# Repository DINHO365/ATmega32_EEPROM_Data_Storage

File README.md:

# ATmega32 EEPROM Data Logging and Configuration Storage System

Demonstrates internal EEPROM read/write on the ATmega32 by letting a
user increment/decrement a value in RAM, save it to EEPROM, read it
back, clear it, and recover it after reset or a power cycle.

## Repository structure

```
ATmega32_EEPROM_Data_Storage/
├── README.md
├── firmware/
│   ├── src/        button.c, display.c, eeprom_storage.c, indicator.c, lcd.c, main.c, uart.c
│   ├── include/    matching headers + config.h
│   └── hex/        firmware.hex / firmware.elf
├── kicad/
│   ├── schematic/  ATmega32_EEPROM_Storage.kicad_sch (+ project files), rendered PDF
│   ├── pcb/        ATmega32_EEPROM_Storage.kicad_pcb (+ project files), rendered PDF
│   └── gerber/     Gerber + drill (.drl) output
├── simulide/
│   ├── circuit/     EEPROM_Storage.sim1
│   └── screenshots/ test-run screenshots
├── documentation/
│   ├── block_diagram.png
│   ├── flowchart.png
│   ├── pin_mapping_table.md
│   ├── eeprom_address_table.md
│   ├── test_results.md
│   ├── erc_report.txt
│   └── drc_report.txt
└── media/
    └── demonstration_video.mp4
```

The schematic and PCB are kept in separate `kicad/schematic/` and
`kicad/pcb/` folders, each with its own copy of the KiCad project file
so either one opens directly in KiCad.

## Firmware

Source lives in `firmware/`, written in C for the ATmega32 at 8 MHz
(adjust `F_CPU` in `firmware/include/config.h` if a different clock is
used).

Build with avr-gcc:

```
cd firmware
make
```

(or open the `firmware/` folder as an MPLAB for VS Code project, using
the same source/include paths.)

### Behavior

| Action            | Result |
|--------------------|--------|
| Power ON / OFF   | Last value loaded from EEPROM and shown as CURRENT |
| INC button (PA0)   | CURRENT increases (clamped at 255) |
| DEC button (PA1)   | CURRENT decreases (clamped at 0) |
| SAVE button (PA2)  | CURRENT written to EEPROM; SAVE_LED + buzzer confirm |
| READ button (PA3)  | SAVED re-read from EEPROM and displayed |
| CLEAR button (PA4) | EEPROM and CURRENT reset to default (0); both LEDs + buzzer confirm |

Display output is a 16x2 HD44780 LCD (RS=PD4, RW=PD5, EN=PD6,
D4-D7=PC4-PC7 via the 16-pin header J1), showing:

```
CURRENT: 025
SAVED:   020
```

`DISPLAY_MODE` in `firmware/include/config.h` can be switched to
`DISPLAY_MODE_USART` to print the same values over USART (9600 baud,
8N1, PD1/TXD) for bench testing without an LCD attached.

### EEPROM layout

See [documentation/eeprom_address_table.md](documentation/eeprom_address_table.md).

### Pin mapping

See [documentation/pin_mapping_table.md](documentation/pin_mapping_table.md).

## SimulIDE simulation

`simulide/circuit/EEPROM_Storage.sim1` mirrors the KiCad PCB wiring
(4-bit LCD interface, RS/RW/EN on PD4-PD6, data lines on PC4-PC7) so
the same firmware behaves identically in simulation and on hardware.
Test results and screenshots for all required test cases are in
[documentation/test_results.md](documentation/test_results.md).

## KiCad design

Schematic and PCB pass ERC and DRC with no violations (see
`documentation/erc_report.txt` and `documentation/drc_report.txt`).
Gerber and drill files are in `kicad/gerber/`.

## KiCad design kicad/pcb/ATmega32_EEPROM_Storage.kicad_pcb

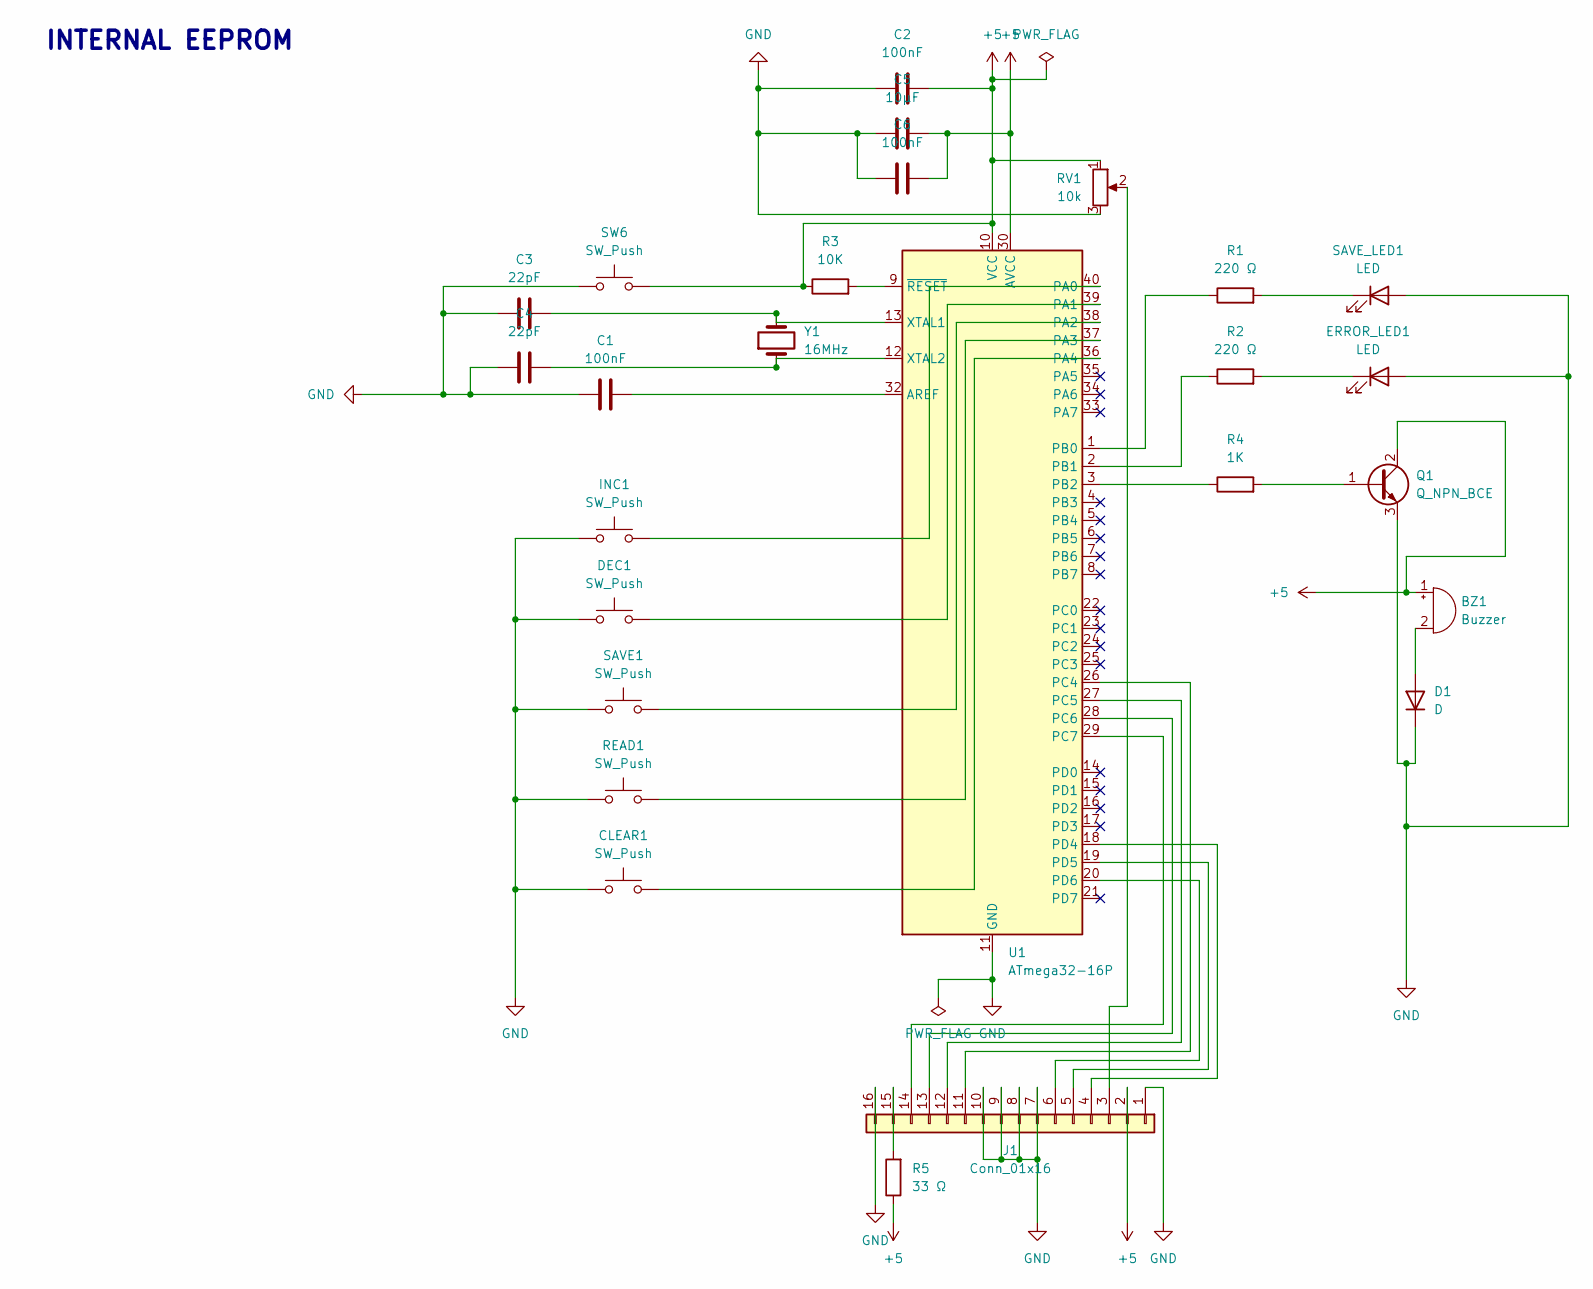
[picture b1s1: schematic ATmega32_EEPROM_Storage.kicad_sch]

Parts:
BZ1: Buzzer; Buzzer_12x9.5RM7.6
C1, C2, C6: 100nF; C_Disc_D5.0mm_W2.5mm_P5.00mm
C3, C4: 22pF; C_Disc_D5.0mm_W2.5mm_P5.00mm
C5: 10µF; C_Disc_D5.0mm_W2.5mm_P5.00mm
CLEAR1: SW_Push; SW_PUSH_6mm
D1: D; LED_D5.0mm
DEC1: SW_Push; SW_PUSH_6mm
ERROR_LED1: LED; LED_D5.0mm
INC1: SW_Push; SW_PUSH_6mm
J1: Conn_01x16; PinHeader_1x16_P2.54mm_Vertical
Q1: Q_NPN_BCE; TO-92_Inline
R1, R2: 220 Ω; R_Axial_DIN0207_L6.3mm_D2.5mm_P7.62mm_Horizontal
R3: 10K; R_Axial_DIN0207_L6.3mm_D2.5mm_P7.62mm_Horizontal
R4: 1K; R_Axial_DIN0207_L6.3mm_D2.5mm_P7.62mm_Horizontal
R5: 33 Ω; R_Axial_DIN0207_L6.3mm_D2.5mm_P7.62mm_Horizontal
READ1: SW_Push; SW_PUSH_6mm
RV1: 10k; Potentiometer_Bourns_3296W_Vertical
SAVE1: SW_Push; SW_PUSH_6mm
SAVE_LED1: LED; LED_D5.0mm
SW6: SW_Push; SW_PUSH_6mm
U1: ATmega32-16P; DIP-40_W15.24mm
Y1: 16MHz; Crystal_HC49-U_Vertical

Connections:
+5: BZ1.1 (+), C2.2, C5.2, C6.2, J1.2, Q1.2 (C), R3.1, R5.1, RV1.1, SW6.2, U1.10 (VCC), U1.30 (AVCC)
GND: C1.1, C2.1, C3.1, C4.1, C5.1, C6.1, CLEAR1.1, D1.1 (K), DEC1.1, ERROR_LED1.2 (A), INC1.1, J1.1, J1.7, J1.8, J1.9, J1.10, J1.16, Q1.3 (E), READ1.1, RV1.3, SAVE1.1, SAVE_LED1.2 (A), SW6.1, U1.11 (GND), U1.31 (GND)
unnamed: BZ1.2 (-), D1.2 (A)
unnamed: ERROR_LED1.1 (K), R2.2
unnamed: J1.3, RV1.2
unnamed: J1.4, U1.18 (PD4)
unnamed: J1.5, U1.19 (PD5)
unnamed: J1.6, U1.20 (PD6)
unnamed: J1.11, U1.26 (PC4)
unnamed: J1.12, U1.27 (PC5)
unnamed: J1.13, U1.28 (PC6)
unnamed: J1.14, U1.29 (PC7)
unnamed: J1.15, R5.2
unnamed: Q1.1 (B), R4.2
unnamed: R1.2, SAVE_LED1.1 (K)
unnamed: C1.2, U1.32 (AREF)
unnamed: INC1.2, U1.40 (PA0)
unnamed: DEC1.2, U1.39 (PA1)
unnamed: SAVE1.2, U1.38 (PA2)
unnamed: READ1.2, U1.37 (PA3)
unnamed: CLEAR1.2, U1.36 (PA4)
unnamed: R1.1, U1.1 (PB0)
unnamed: R2.1, U1.2 (PB1)
unnamed: R4.1, U1.3 (PB2)
unnamed: C3.2, U1.13 (XTAL1), Y1.2
unnamed: C4.2, U1.12 (XTAL2), Y1.1
unnamed: R3.2, U1.9 (~RESET)

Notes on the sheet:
INTERNAL EEPROM

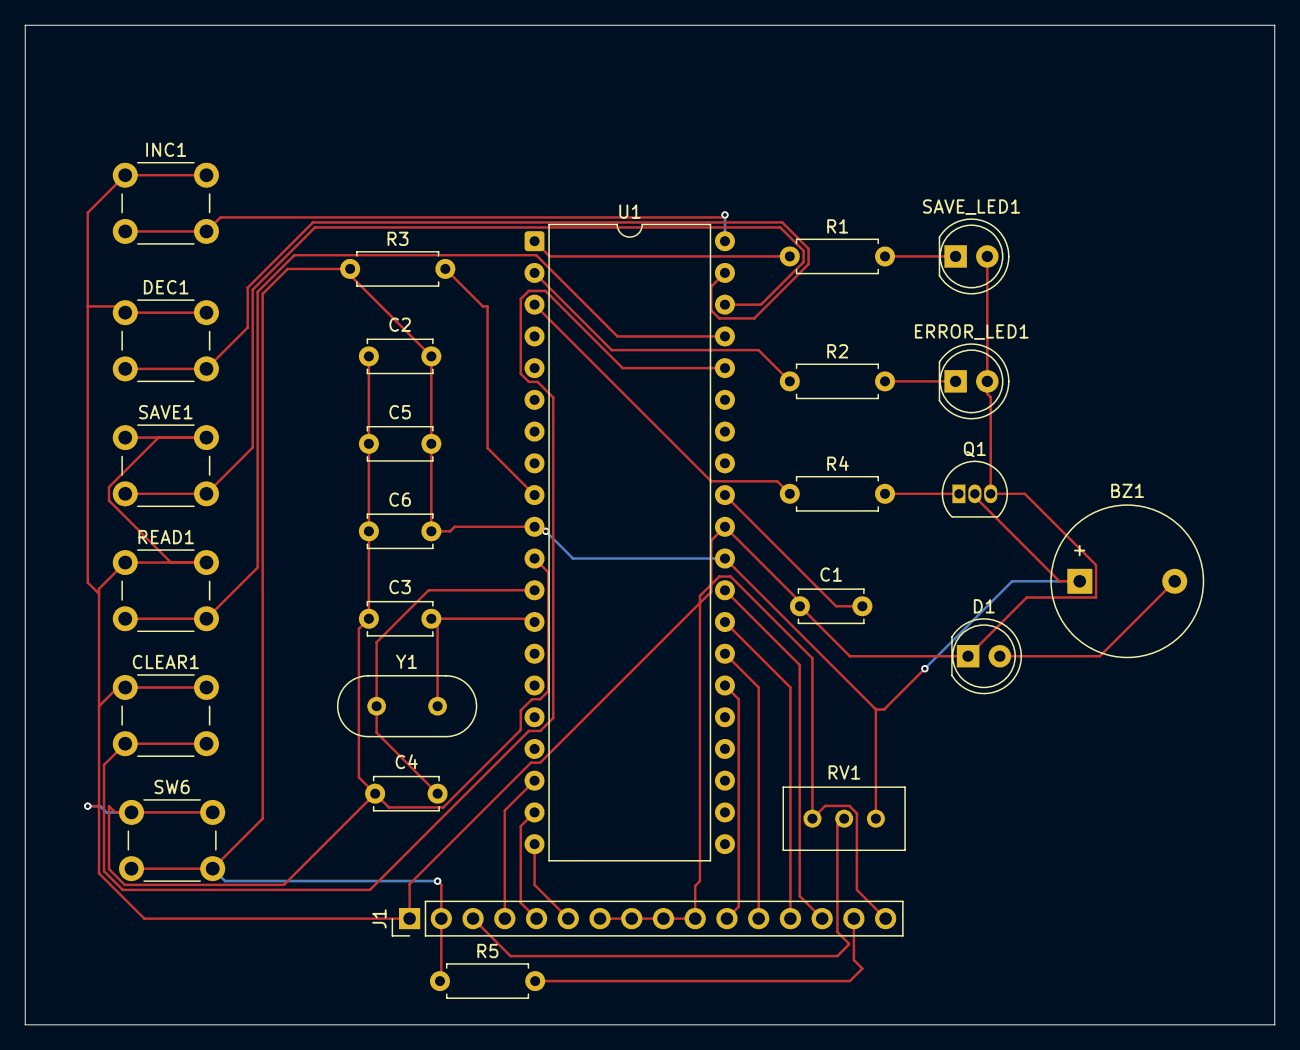
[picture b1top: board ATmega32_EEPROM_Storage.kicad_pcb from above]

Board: 2 copper layers, 100.0 x 80.0 mm, 26 parts (0 on the bottom side), 27 nets.

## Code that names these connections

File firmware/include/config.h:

/*
 * config.h
 * Project 16: EEPROM-Based Data Logging and Configuration Storage System
 * Target: ATmega32, F_CPU = 8,000,000 Hz (internal/external clock, adjust if different)
 */

#ifndef CONFIG_H
#define CONFIG_H

#ifndef F_CPU
#define F_CPU 8000000UL
#endif

#include <avr/io.h>

/* ---------------------------------------------------------------------
 * Display backend selection
 * The project's KiCad schematic/PCB wires a 16-pin HD44780 LCD header
 * (J1) to PD4/PD5/PD6 (RS/RW/EN) and PC4-PC7 (D4-D7); PD0/PD1 (RXD/TXD)
 * are left unconnected on that board, so DISPLAY_MODE_LCD is the
 * correct default for the actual hardware. DISPLAY_MODE_USART remains
 * available for bench testing on a breadboard with a serial terminal.
 * --------------------------------------------------------------------- */
#define DISPLAY_MODE_USART 0
#define DISPLAY_MODE_LCD   1

#ifndef DISPLAY_MODE
#define DISPLAY_MODE DISPLAY_MODE_LCD
#endif

/* ---------------------------------------------------------------------
 * Push buttons - PORTA, active LOW (internal pull-ups enabled)
 * --------------------------------------------------------------------- */
#define BTN_PORT   PORTA
#define BTN_DDR    DDRA
#define BTN_PIN    PINA

#define BTN_INC    PA0   /* Increment button */
#define BTN_DEC    PA1   /* Decrement button */
#define BTN_SAVE   PA2   /* Save button      */
#define BTN_READ   PA3   /* Read button       */
#define BTN_CLEAR  PA4   /* Clear button      */

/* ---------------------------------------------------------------------
 * LEDs and buzzer - PORTB
 * --------------------------------------------------------------------- */
#define IND_PORT   PORTB
#define IND_DDR    DDRB

#define SAVE_LED   PB0   /* Save / status LED */
#define ERROR_LED  PB1   /* Error LED         */
#define BUZZER     PB2   /* Buzzer            */

/* ---------------------------------------------------------------------
 * EEPROM address map
 * --------------------------------------------------------------------- */
#define EEPROM_ADDR_MAGIC    0x00   /* marks EEPROM as initialized              */
#define EEPROM_ADDR_VALUE    0x01   /* explicitly saved value (SAVE button)     */
#define EEPROM_ADDR_CURRENT  0x02   /* auto-saved value (every INC/DEC press)   */
#define EEPROM_MAGIC_BYTE    0xAA   /* sentinel written after first save        */

/* ---------------------------------------------------------------------
 * Value limits
 * --------------------------------------------------------------------- */
#define VALUE_MIN     0
#define VALUE_MAX     255
#define VALUE_DEFAULT 0

/* ---------------------------------------------------------------------
 * Timing
 * --------------------------------------------------------------------- */
#define DEBOUNCE_DELAY_MS  25
#define BEEP_DELAY_MS      250
#define LED_PULSE_MS       400

#endif /* CONFIG_H */

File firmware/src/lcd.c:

/*
 * lcd.c
 * Pin mapping taken from the project's actual KiCad schematic/PCB
 * (16-pin LCD header J1, ATmega32 net labels):
 *   RS = PD4, RW = PD5, EN = PD6, D4-D7 = PC4-PC7
 * RW is wired to a GPIO (not tied to GND), so the driver must hold it
 * low to keep the LCD permanently in write mode.
 */

#include "lcd.h"
#include "config.h"
#include <util/delay.h>

#define LCD_CTRL_PORT  PORTD
#define LCD_CTRL_DDR   DDRD
#define LCD_RS         PD4
#define LCD_RW         PD5
#define LCD_EN         PD6

#define LCD_DATA_PORT  PORTC
#define LCD_DATA_DDR   DDRC
#define LCD_D4         PC4
#define LCD_D5         PC5
#define LCD_D6         PC6
#define LCD_D7         PC7

static void lcd_pulse_enable(void)
{
    LCD_CTRL_PORT |= (1 << LCD_EN);
    _delay_us(1);
    LCD_CTRL_PORT &= (unsigned char)~(1 << LCD_EN);
    _delay_us(100);
}

static void lcd_write_nibble(unsigned char nibble)
{
    LCD_DATA_PORT &= (unsigned char)~((1 << LCD_D4) | (1 << LCD_D5) | (1 << LCD_D6) | (1 << LCD_D7));
    if (nibble & 0x01) LCD_DATA_PORT |= (1 << LCD_D4);
    if (nibble & 0x02) LCD_DATA_PORT |= (1 << LCD_D5);
    if (nibble & 0x04) LCD_DATA_PORT |= (1 << LCD_D6);
    if (nibble & 0x08) LCD_DATA_PORT |= (1 << LCD_D7);
    lcd_pulse_enable();
}

static void lcd_write_byte(unsigned char value, unsigned char is_data)
{
    if (is_data) {
        LCD_CTRL_PORT |= (1 << LCD_RS);
    } else {
        LCD_CTRL_PORT &= (unsigned char)~(1 << LCD_RS);
    }
    lcd_write_nibble((unsigned char)(value >> 4));
    lcd_write_nibble((unsigned char)(value & 0x0F));
}

void LCD_Command(unsigned char cmd)
{
    lcd_write_byte(cmd, 0);
    if (cmd == 0x01 || cmd == 0x02) {
        _delay_ms(2); /* clear / home need extra time */
    }
}

void LCD_Char(char c)
{
    lcd_write_byte((unsigned char)c, 1);
}

void LCD_String(const char *str)
{
    while (*str) {
        LCD_Char(*str);
        str++;
    }
}

void LCD_SetCursor(unsigned char row, unsigned char col)
{
    unsigned char addr = (row == 0) ? (0x80 + col) : (0xC0 + col);
    LCD_Command(addr);
}

void LCD_Clear(void)
{
    LCD_Command(0x01);
}

void LCD_Init(void)
{
    LCD_CTRL_DDR |= (1 << LCD_RS) | (1 << LCD_RW) | (1 << LCD_EN);
    LCD_DATA_DDR |= (1 << LCD_D4) | (1 << LCD_D5) | (1 << LCD_D6) | (1 << LCD_D7);

    LCD_CTRL_PORT &= (unsigned char)~((1 << LCD_RS) | (1 << LCD_RW) | (1 << LCD_EN));
    LCD_DATA_PORT &= (unsigned char)~((1 << LCD_D4) | (1 << LCD_D5) | (1 << LCD_D6) | (1 << LCD_D7));

    _delay_ms(40); /* power-on settle */

    /* HD44780 4-bit init sequence */
    lcd_write_nibble(0x03);
    _delay_ms(5);
    lcd_write_nibble(0x03);
    _delay_us(150);
    lcd_write_nibble(0x03);
    lcd_write_nibble(0x02); /* switch to 4-bit mode */

    LCD_Command(0x28); /* 4-bit, 2 line, 5x8 font */
    LCD_Command(0x0C); /* display ON, cursor OFF */
    LCD_Command(0x06); /* auto-increment cursor */
    LCD_Command(0x01); /* clear display */
}

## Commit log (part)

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2026-06-28 Initial project structure created
2026-06-28 Added EEPROM read and write functions
2026-06-28 Added button control and LED/buzzer indicator firmware
2026-06-28 Added LCD/serial display output support and main firmware logic
2026-06-28 Added KiCad schematic design
2026-06-28 Added PCB layout and Gerber files
2026-06-28 Added SimulIDE simulation circuit and screenshots
2026-06-28 Added EEPROM test results, block diagram/flowchart, and project documentation
2026-06-28 Clean up documentation and simplify test screenshots
